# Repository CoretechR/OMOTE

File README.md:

# OMOTE - Open Universal Remote - Firmware

[][link1]

## Overview

This it the ESP32 arduino based firmware for the OMOTE - Open Universal Remote.

To run this firmware, you have two options
*  run it on the [OMOTE ESP32 Hardware](https://github.com/OMOTE-Community/OMOTE-Hardware/)
*  run it in the simulator on Linux, macOs or Windows

### The state of this project

#### Software
The software can be adjusted to your needs. You can add your own amplifier, TV and media player. Smart home devices can be controlled with MQTT. The software is an example made up of:
* a TV and an amplifier controlled with infrared
* a Fire TV media player controlled with BLE (bluetooth keyboard)
* some smart home devices controlled with MQTT
* an IR receiver for decoding the IR codes from your remote

Please see the [wiki on how to understand and modify the firmware.](https://github.com/OMOTE-Community/OMOTE-Firmware/wiki/How-to-understand-and-modify-the-firmware)

You need to have PlatformIO running, and you need to know how to compile and flash your own firmware with PlatformIO. There is no prebuild firmware.

The remote can be charged and programmed via its USB-C port. Open the PlatformIO project to compile and upload the code to the ESP32.

As a long term goal, maybe a prebuild firmware will be published, where you can configure your OMOTE via a web interface.

### LVGL GUI simulator for Windows, Linux, and macOS

A simulator for running the LVGL UI on your local Windows, Linux, or macOS machine is available.

You can run the simulator in Visual Studio Code with PlatformIO. No need for any other compiler or development environment (no Visual Studio needed as often done in other LVGL simulators).
<div align="center">
  
</div>

For details, please see the [wiki for the software simulator for fast creating and testing of LVGL GUIs.](https://github.com/OMOTE-Community/OMOTE-Firmware/wiki/Software-simulator-for-fast-creating-and-testing-of-LVGL-GUIs)

### To Dos for software

Long term goals (not yet scheduled)
- [ ] Add an interface for graphically editing the configuration
- [ ] Store the configuration in Flash (e.g. as a editable json file)

See the [open issues](https://github.com/OMOTE-Community/OMOTE-Firmware/issues) and [discussions](https://github.com/OMOTE-Community/OMOTE-Firmware/discussions) for a full list of proposed features (and known issues).

## Contributing

If you have a suggestion for an improvement, please fork the repo and create a pull request. You can also simply open an issue or for more general feature requests, head over to the [discussions](https://github.com/OMOTE-Community/OMOTE-Firmware/discussions).

## License

Distributed under the GPL v3 License. See [LICENSE](https://github.com/OMOTE-Community/OMOTE-Firmware/blob/main/LICENSE) for more information.

## Contact

[][link1]

Join the OMOTE Discord: [https://discord.gg/5PnYFAsKsG](https://discord.gg/5PnYFAsKsG)

[link1]: https://discord.gg/5PnYFAsKsG

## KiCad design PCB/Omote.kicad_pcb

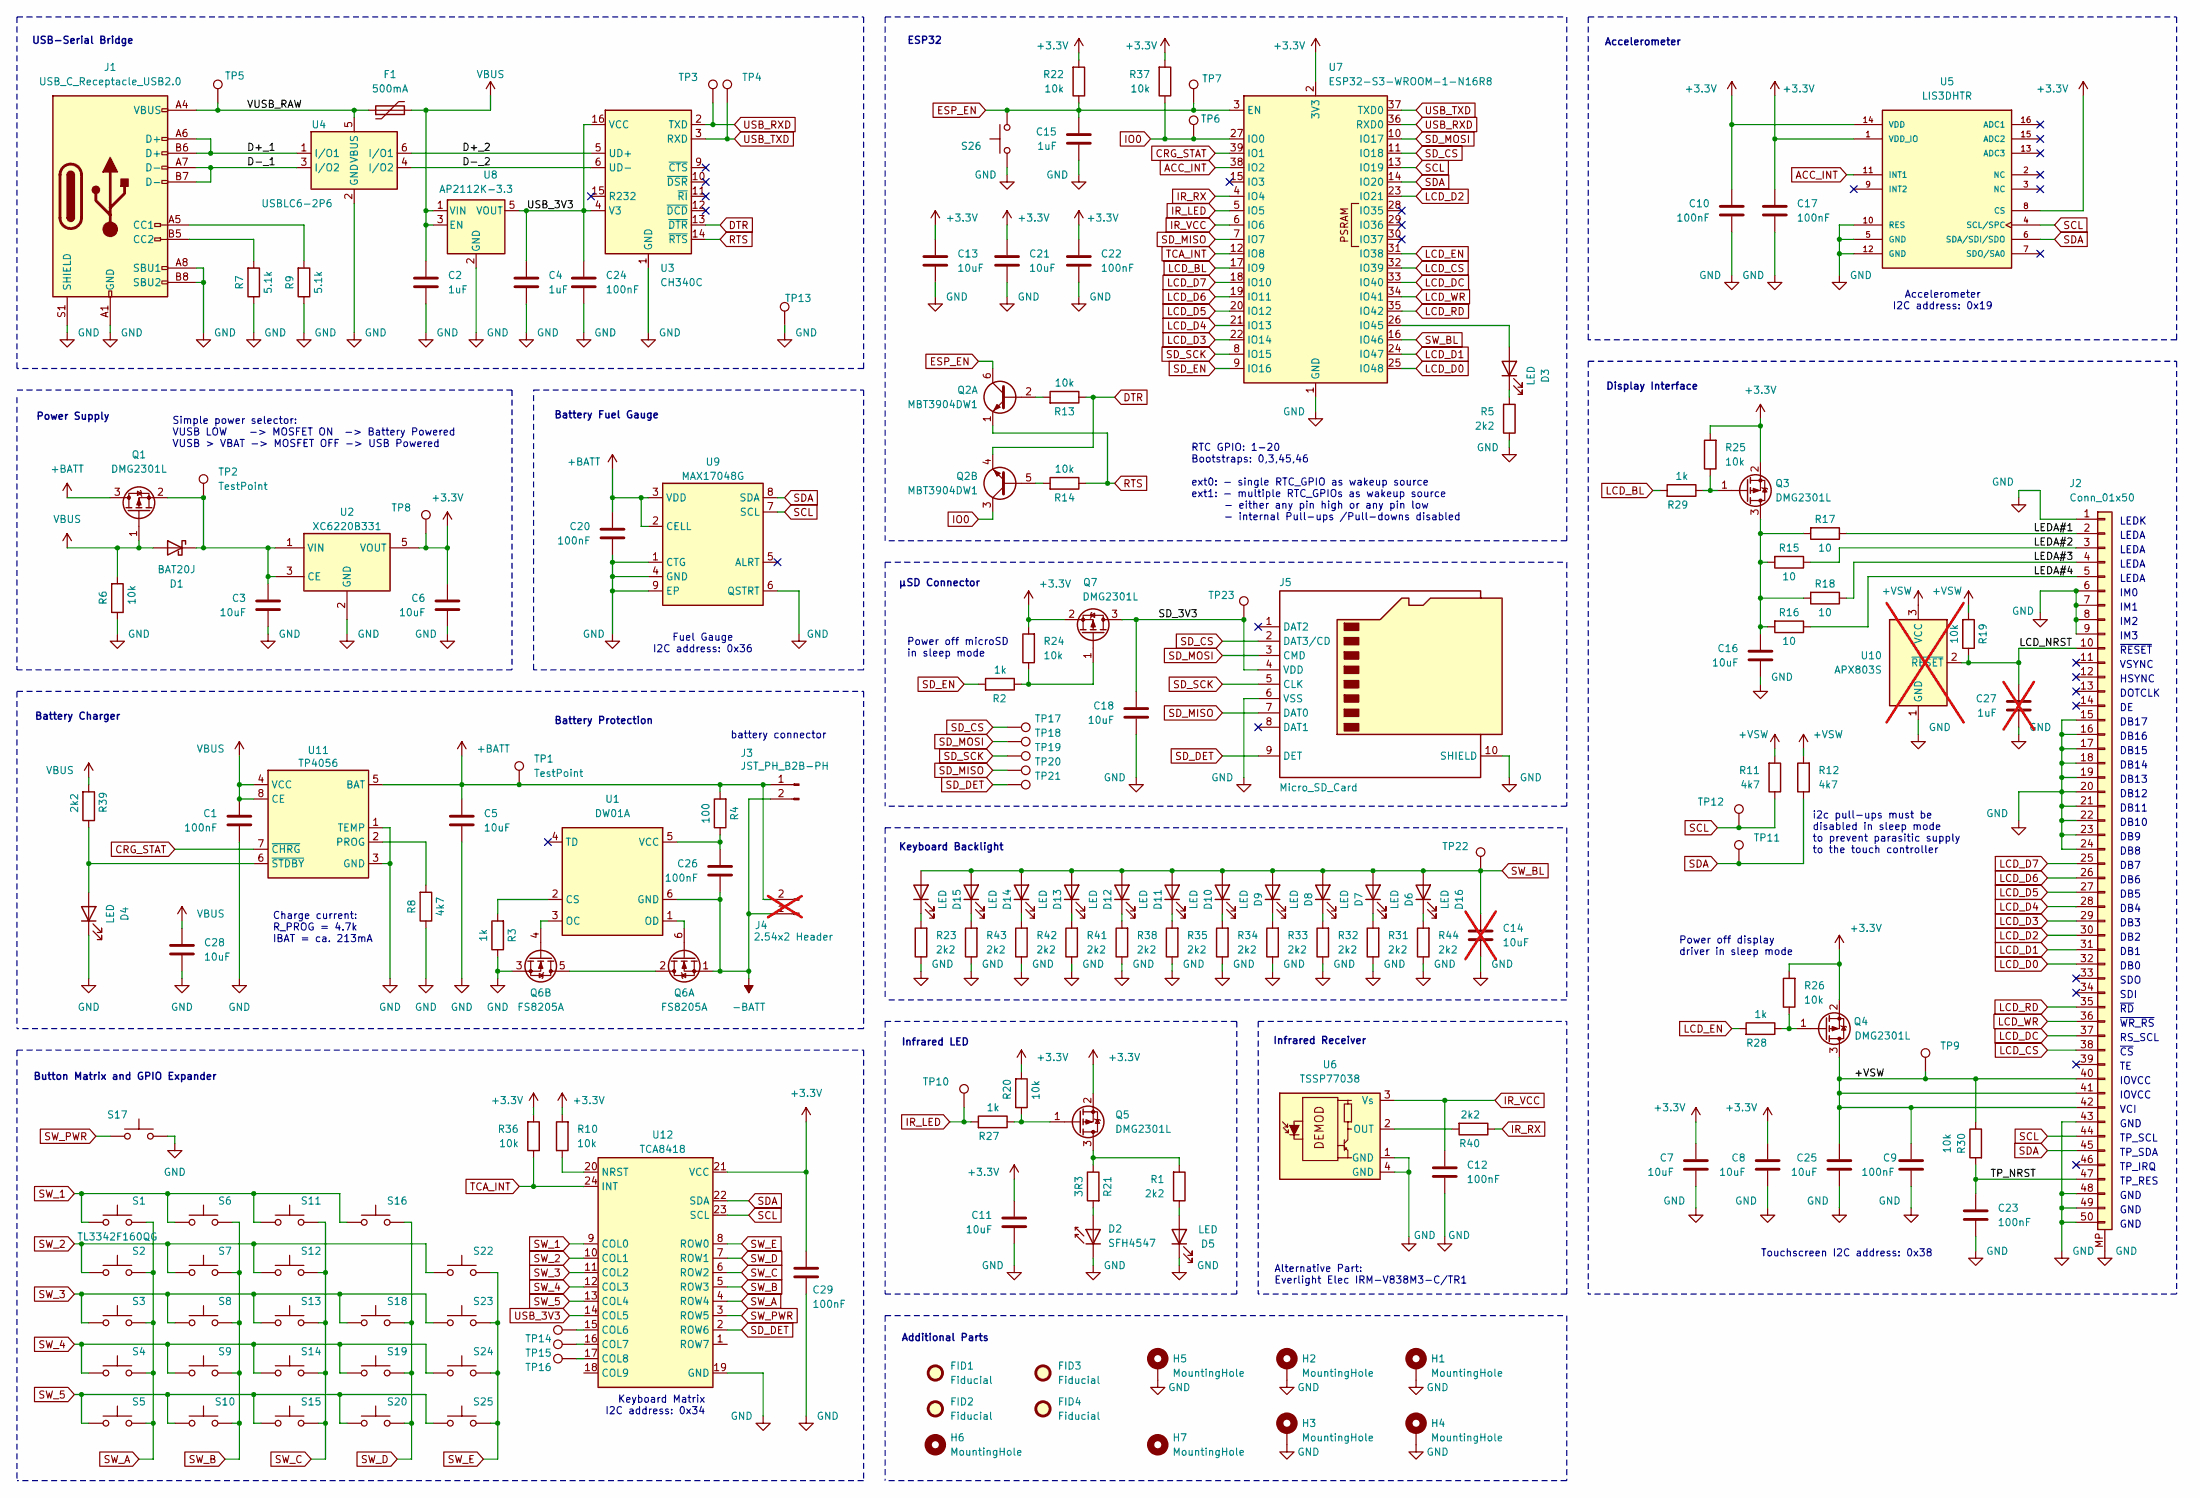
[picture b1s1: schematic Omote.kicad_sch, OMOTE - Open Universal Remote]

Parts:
C1, C9, C10, C12, C17, C20, C22, C23, C24, C26, C29: 100nF; C_0603_1608Metric; LCSC C1591
C2, C4, C15: 1uF; C_0603_1608Metric; LCSC C15849
C3, C5, C6, C7, C8, C11, C13, C16, C18, C21, C25, C28: 10uF; C_0805_2012Metric; LCSC C15850
C14: 10uF; C_0805_2012Metric; LCSC C15850; not fitted
C27: 1uF; C_0603_1608Metric; not fitted
D1: BAT20J; D_SOD-323; LCSC C155590
D2: SFH4547; LED_5mm_Side_Mount; LCSC C405273
D3, D4, D5: LED; LED_0603_1608Metric; LCSC C965807
D6, D7, D8, D9, D10, D11, D12, D13, D14, D15, D16: LED; LED_0603_1608Metric; LCSC C84265
F1: 500mA; Fuse_1206_3216Metric_Pad1.42x1.75mm_HandSolder; LCSC C220146
FID1, FID2, FID3, FID4: Fiducial; Fiducial_1mm_Mask2mm
H1, H2, H3, H5: MountingHole; MountingHole_3.2mm_M3_Pad_Via
H4: MountingHole; MountingHole_3.2mm_M3
H6, H7: MountingHole; MountingHole_2.5mm
J1: USB_C_Receptacle_USB2.0; USB_C_Receptacle_HRO_TYPE-C-31-M-12; LCSC C2982555
J2: Conn_01x50; TFT_2.83IN_240X320_50PIN; LCSC C11098
J3: JST_PH_B2B-PH; JST_PH_B2B-PH-SM4-TB_1x02-1MP_P2.00mm_Vertical; LCSC C160352
J4: 2.54x2 Header; PinHeader_1x02_P2.54mm_Vertical; not fitted
J5: Micro_SD_Card; MicroSD Slot TF-01A; LCSC C20613191
Q1, Q3, Q4, Q5, Q7: DMG2301L; SOT-23; LCSC C102619
Q2: MBT3904DW1; SOT-363_SC-70-6; LCSC C110150
Q6: FS8205A; SOT-23-6; LCSC C908265
R1, R5, R23, R31, R32, R33, R34, R35, R38, R39, R40, R41, R42, R43, R44: 2k2; R_0603_1608Metric; LCSC C114662
R2, R3, R27, R28, R29: 1k; R_0603_1608Metric; LCSC C22548
R4: 100; R_0603_1608Metric; LCSC C125923
R6, R10, R13, R14, R19, R20, R22, R24, R25, R26, R30, R36, R37: 10k; R_0603_1608Metric; LCSC C98220
R7, R9: 5.1k; R_0603_1608Metric; LCSC C105580
R8, R11, R12: 4k7; R_0603_1608Metric; LCSC C99782
R15, R16, R17, R18: 10; R_0603_1608Metric; LCSC C109318
R21: 3R3; R_0805_2012Metric; LCSC C2849062
S1, S2, S3, S4, S5, S6, S7, S8, S9, S10, S11, S12, S13, S14, S15, S16, S17, S18, S19, S20, S22, S23, S24, S25, S26: TL3342F160QG; SW_SPST_TL3342; LCSC C778172
TP1, TP2, TP3, TP4, TP5, TP6, TP7, TP8, TP9, TP10, TP11, TP12, TP13, TP14, TP15, TP16, TP17, TP18, TP19, TP20, TP21, TP22, TP23: TestPoint; TestPoint_Pad_D1.5mm
U1: DW01A; SOT-23-6; LCSC C18164398
U2: XC6220B331; SOT-23-5; LCSC C86534
U3: CH340C; SOIC-16_3.9x9.9mm_P1.27mm; LCSC C84681
U4: USBLC6-2P6; SOT-666; LCSC C2827693
U5: LIS3DHTR; XDCR_LIS3DHTR; PARTREV 2; LCSC C15134
U6: TSSP77038; Heimdall vertical; LCSC C3291489
U7: ESP32-S3-WROOM-1-N16R8; ESP32-S3-WROOM-1; LCSC C2913202
U8: AP2112K-3.3; SOT-23-5; LCSC C51118
U9: MAX17048G; TDFN-8-1EP_2x2mm_P0.5mm_EP0.8x1.2mm; LCSC C2682616
U10: APX803S; SOT-23; not fitted
U11: TP4056; Infineon_PG-DSO-8-27_3.9x4.9mm_EP2.65x3mm; LCSC C725790
U12: TCA8418; HVQFN-24-1EP_4x4mm_P0.5mm_EP2.5x2.5mm; LCSC C138713

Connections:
+3.3V: C6.1, C7.2, C8.2, C10.1, C11.2, C13.2, C17.1, C21.2, C22.1, C29.1, Q3.2 (S), Q4.2 (S), Q5.2 (S), Q7.2 (S), R10.2, R20.2, R22.2, R24.2, R25.2, R26.2, R36.2, R37.2, TP8.1, U2.5 (VOUT), U5.1 (VDD_IO), U5.8 (CS), U5.14 (VDD), U7.2 (3V3), U12.21 (VCC)
+BATT: C5.2, C20.1, J3.1, J4.2, Q1.3 (D), R4.2, TP1.1, U9.2 (CELL), U9.3 (VDD), U11.5 (BAT)
+VSW: C9.1, C25.2, J2.40, J2.41, J2.42 (Pin_41), Q4.3 (D), R11.2, R12.2, R19.2, R30.1, TP9.1, U10.3 (VCC)
-BATT: C26.2, J3.2, J4.1, Q6.1 (S), U1.6 (GND)
/D+_1: J1.A6 (D+), J1.B6 (D+), U4.1 (I/O1)
/D+_2: U3.5 (UD+), U4.6 (I/O1)
/D-_1: J1.A7 (D-), J1.B7 (D-), U4.3 (I/O2)
/D-_2: U3.6 (UD-), U4.4 (I/O2)
/LCD_NRST: C27.2, J2.10, R19.1, U10.2 (~RESET)
/LEDA#1: J2.2, R17.1
/LEDA#2: J2.3, R15.1
/LEDA#3: J2.4, R18.1
/LEDA#4: J2.5, R16.1
/SD_3V3: C18.2, J5.4 (VDD), Q7.3 (D), TP23.1
/TP_NRST: C23.2, J2.47, R30.2
/VUSB_RAW: F1.1, J1.A4 (VBUS), J1.A9 (VBUS), J1.B4 (VBUS), J1.B9 (VBUS), TP5.1, U4.5 (VBUS)
ACC_INT: U5.11 (INT1), U7.38 (IO2)
CRG_STAT: U7.39 (IO1), U11.7 (~CHRG)
DTR: Q2.4 (E2), R13.1, U3.13 (~DTR)
ESP_EN: C15.2, Q2.6 (C1), R22.1, S26.2, TP7.1, U7.3 (EN)
GND: C1.2, C2.2, C3.1, C4.2, C5.1, C6.2, C7.1, C8.1, C9.2, C10.2, C11.1, C12.2, C13.1, C14.1, C15.1, C16.1, C17.2, C18.1, C20.2, C21.1, C22.2, C23.1, C24.2, C25.1, C27.1, C28.1, C29.2, D2.1 (K), D4.1 (K), D5.1 (K), H1.1, H2.1, H3.1, H4.1, H5.1, J1.A1 (GND), J1.A8 (SBU1), J1.A12 (GND), J1.B1 (GND), J1.B8 (SBU2), J1.B12 (GND), J1.S1 (SHIELD), J2.1, J2.6, J2.7, J2.8, J2.9, J2.15, J2.16, J2.17, J2.18, J2.19, J2.20, J2.21, J2.22, J2.23, J2.24, J2.43, J2.48, J2.49, J2.50, J2.MP, J5.6 (VSS), J5.10 (SHIELD), Q6.3 (S), R3.1, R5.1, R6.1, R7.1, R8.1, R9.1, R23.1, R31.1, R32.1, R33.1, R34.1, R35.1, R38.1, R41.1, R42.1, R43.1, R44.1, S17.1, S26.1, TP13.1, U2.2 (GND), U3.1 (GND), U4.2 (GND), U5.5 (GND), U5.10 (RES), U5.12 (GND), U6.1 (GND), U6.4 (GND), U7.1 (GND), U7.40 (GND), U7.41 (GND), U8.2 (GND), U9.1 (CTG), U9.4 (GND), U9.6 (QSTRT), U9.9 (EP), U10.1 (GND), U11.1 (TEMP), U11.3 (GND), U11.9 (GND), U12.19 (GND)
IO0: Q2.3 (C2), R37.1, TP6.1, U7.27 (IO0)
IR_LED: R27.2, TP10.1, U7.5 (IO5)
IR_RX: R40.1, U7.4 (IO4)
IR_VCC: C12.1, U6.3 (Vs), U7.6 (IO6)
LCD_BL: R29.2, U7.17 (IO9)
LCD_CS: J2.38, U7.32 (IO39)
LCD_D0: J2.32, U7.25 (IO48)
LCD_D1: J2.31, U7.24 (IO47)
LCD_D2: J2.30, U7.23 (IO21)
LCD_D3: J2.29, U7.22 (IO14)
LCD_D4: J2.28, U7.21 (IO13)
LCD_D5: J2.27, U7.20 (IO12)
LCD_D6: J2.26, U7.19 (IO11)
LCD_D7: J2.25, U7.18 (IO10)
LCD_DC: J2.37, U7.33 (IO40)
LCD_EN: R28.2, U7.31 (IO38)
LCD_RD: J2.35, U7.35 (IO42)
LCD_WR: J2.36, U7.34 (IO41)
unnamed: C3.2, D1.1 (K), Q1.2 (S), TP2.1, U2.1 (VIN), U2.3 (CE)
unnamed: D2.2 (A), R21.2
unnamed: D3.2 (A), U7.26 (IO45)
unnamed: D3.1 (K), R5.2
unnamed: D4.2 (A), R39.1, U11.6 (~STDBY)
unnamed: D5.2 (A), R1.1
unnamed: D6.1 (K), R31.2
unnamed: D7.1 (K), R32.2
unnamed: D8.1 (K), R33.2
unnamed: D9.1 (K), R34.2
unnamed: D10.1 (K), R35.2
unnamed: D11.1 (K), R38.2
unnamed: D12.1 (K), R41.2
unnamed: D13.1 (K), R42.2
unnamed: D14.1 (K), R43.2
unnamed: D15.1 (K), R23.2
unnamed: D16.1 (K), R44.2
unnamed: J1.A5 (CC1), R9.2
unnamed: J1.B5 (CC2), R7.2
unnamed: Q2.2 (B1), R13.2
unnamed: Q2.5 (B2), R14.2
unnamed: C16.2, Q3.3 (D), R15.2, R16.2, R17.2, R18.2
unnamed: Q3.1 (G), R25.1, R29.1
unnamed: Q4.1 (G), R26.1, R28.1
unnamed: Q5.3 (D), R1.2, R21.1
unnamed: Q5.1 (G), R20.1, R27.1
unnamed: Q6.2 (D), Q6.5 (D)
unnamed: Q6.6 (G), U1.1 (OD)
unnamed: Q6.4 (G), U1.3 (OC)
unnamed: Q7.1 (G), R2.1, R24.1
unnamed: R3.2, U1.2 (CS)
unnamed: C26.1, R4.1, U1.5 (VCC)
unnamed: R40.2, U6.2 (OUT)
unnamed: R8.2, U11.2 (PROG)
unnamed: TP14.1, U12.15 (COL6)
unnamed: TP15.1, U12.16 (COL7)
unnamed: TP16.1, U12.17 (COL8)
unnamed: R10.1, U12.20 (NRST)
RTS: Q2.1 (E1), R14.1, U3.14 (~RTS)
SCL: J2.44, R11.1, TP12.1, U5.4 (SCL/SPC), U7.13 (IO19), U9.7 (SCL), U12.23 (SCL)
SDA: J2.45, R12.1, TP11.1, U5.6 (SDA/SDI/SDO), U7.14 (IO20), U9.8 (SDA), U12.22 (SDA)
SD_CS: J5.2 (DAT3/CD), TP17.1, U7.11 (IO18)
SD_DET: J5.9 (DET), TP21.1, U12.2 (ROW6)
SD_EN: R2.2, U7.9 (IO16)
SD_MISO: J5.7 (DAT0), TP20.1, U7.7 (IO7)
SD_MOSI: J5.3 (CMD), TP18.1, U7.10 (IO17)
SD_SCK: J5.5 (CLK), TP19.1, U7.8 (IO15)
SW_1: S1.1, S6.1, S11.1, S16.1, U12.9 (COL0)
SW_2: S2.1, S7.1, S12.1, S22.1, U12.10 (COL1)
SW_3: S3.1, S8.1, S13.1, S18.1, S23.1, U12.11 (COL2)
SW_4: S4.1, S9.1, S14.1, S19.1, S24.1, U12.12 (COL3)
SW_5: S5.1, S10.1, S15.1, S20.1, S25.1, U12.13 (COL4)
SW_A: S1.2, S2.2, S3.2, S4.2, S5.2, U12.4 (ROW4)
SW_B: S6.2, S7.2, S8.2, S9.2, S10.2, U12.5 (ROW3)
SW_BL: C14.2, D6.2 (A), D7.2 (A), D8.2 (A), D9.2 (A), D10.2 (A), D11.2 (A), D12.2 (A), D13.2 (A), D14.2 (A), D15.2 (A), D16.2 (A), TP22.1, U7.16 (IO46)
SW_C: S11.2, S12.2, S13.2, S14.2, S15.2, U12.6 (ROW2)
SW_D: S16.2, S18.2, S19.2, S20.2, U12.7 (ROW1)
SW_E: S22.2, S23.2, S24.2, S25.2, U12.8 (ROW0)
SW_PWR: S17.2, U12.3 (ROW5)
TCA_INT: R36.1, U7.12 (IO8), U12.24 (INT)
USB_3V3: C4.1, C24.1, U3.4 (V3), U3.16 (VCC), U8.5 (VOUT), U12.14 (COL5)
USB_RXD: TP3.1, U3.2 (TXD), U7.36 (RXD0)
USB_TXD: TP4.1, U3.3 (RXD), U7.37 (TXD0)
VBUS: C1.1, C2.1, C28.2, D1.2 (A), F1.2, Q1.1 (G), R6.2, R39.2, U8.1 (VIN), U8.3 (EN), U11.4 (VCC), U11.8 (CE)

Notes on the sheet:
DB6
Accelerometer I2C address: 0x19
DB11
DB14
IM2
DB10
Infrared Receiver
Display Interface
LEDA
DB0
GND
DB16
Alternative Part: Everlight Elec IRM-V838M3-C/TR1
TP_RES
TP_IRQ
LEDK
IM1
IOVCC
Battery Fuel Gauge
~{RESET}
ESP32
RTC GPIO: 1-20 Bootstraps: 0,3,45,46 ext0: - single RTC_GPIO as wakeup source ext1: - multiple RTC_GPIOs as wakeup source - either any pin high or any pin low - internal Pull-ups /Pull-downs disabled
Battery Protection
IM3
DB5
Additional Parts
USB-Serial Bridge
Charge current: R_PROG = 4.7k IBAT = ca. 213mA
DB17
TP_SDA
DB7
DB12
DB1
DOTCLK
~{WR_RS}
Infrared LED
µSD Connector
SDI
DB13
DB4

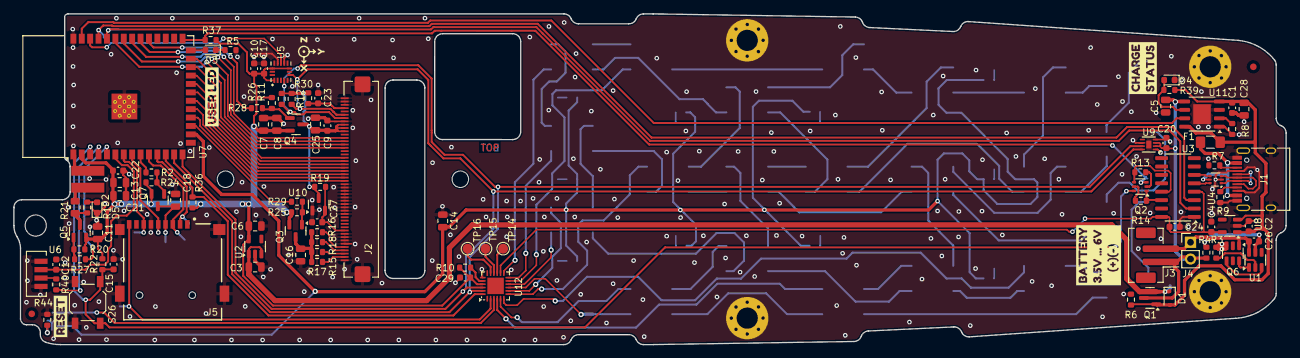
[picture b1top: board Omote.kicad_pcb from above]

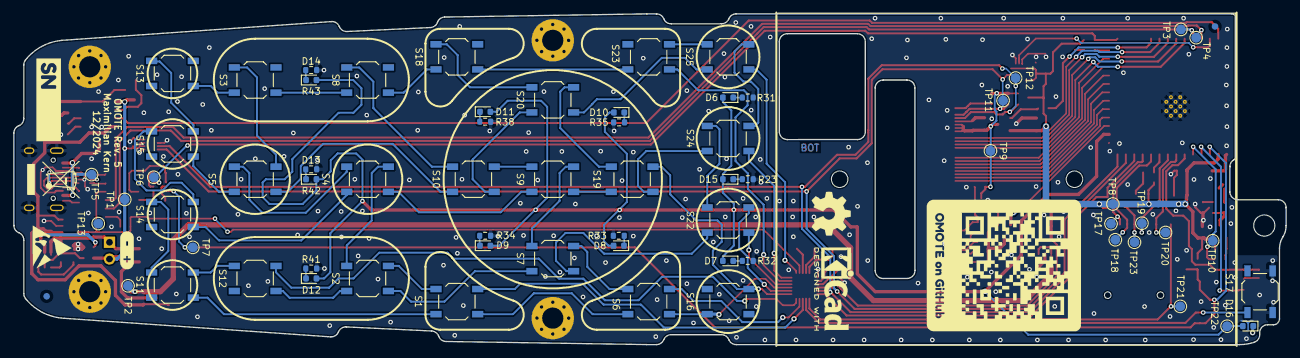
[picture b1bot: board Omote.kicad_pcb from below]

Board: 2 copper layers, 192.4 x 50.0 mm, 181 parts (69 on the bottom side), 103 nets.

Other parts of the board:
kibuzzard-63D97EAF: G***; kibuzzard-63D97EAF
kibuzzard-64A91BF0: G***; kibuzzard-64A91BF0
kibuzzard-64A91C1C: G***; kibuzzard-64A91C1C
kibuzzard-64A91C24: G***; kibuzzard-64A91C24
kibuzzard-643EE5B9: G***; kibuzzard-643EE5B9
kibuzzard-643EE8B3: G***; kibuzzard-643EE8B3
kibuzzard-643EE46C: G***; kibuzzard-643EE46C
kibuzzard-643EE600: G***; kibuzzard-643EE600
kibuzzard-644014FA: G***; kibuzzard-644014FA

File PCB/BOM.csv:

Item,Quantity,Designator,Value,Footprint,LCSC Part #,Comment
1,11,C1; C10; C12; C17; C20; C22; C23; C24; C26; C29; C9,100nF,0603,C1591,
2,12,C11; C13; C16; C18; C21; C25; C28; C3; C5; C6; C7; C8,10uF,805,C15850,
3,3,C15; C2; C4,1uF,0603,C15849,
4,1,D1,BAT20J,D_SOD-323,C155590,
5,14,D10; D11; D12; D13; D14; D15; D16; D3; D4; D5; D6; D7; D8; D9,LED,0603,C965807,
6,1,D2,SFH4547,LED_5mm_Side_Mount,C405273,
7,1,F1,500mA,1206,C220146,
8,1,J1,USB_C_Receptacle_USB2.0,USB_C_Receptacle_HRO_TYPE-C-31-M-12,C2982555,
9,1,J2,Conn_01x50,TFT_2.83IN_240X320_50PIN,C11098,
10,1,J3,JST_PH_B2B-PH,JST_PH_B2B-PH-SM4-TB_1x02-1MP_P2.00mm_Vertical,C160352,
11,1,J5,Micro_SD_Card,MicroSD Slot TF-01A,C20613191,
12,5,Q1; Q3; Q4; Q5; Q7,DMG2301L,SOT-23,C102619,
13,1,Q2,MBT3904DW1,SOT-363_SC-70-6,C110150,
14,1,Q6,FS8205A,SOT-23-6,C908265,
15,15,R1; R23; R31; R32; R33; R34; R35; R38; R39; R40; R41; R42; R43; R44; R5,2k2,0603,C114662,
16,13,R10; R13; R14; R19; R20; R22; R24; R25; R26; R30; R36; R37; R6,10k,0603,C98220,
17,3,R11; R12; R8,4k7,0603,C99782,
18,4,R15; R16; R17; R18,10,0603,C109318,
19,1,R21,3R3,805,C2849062,
20,5,R2; R3; R27; R28; R29,1k,0603,C22548,
21,1,R4,100,0603,C125923,
22,2,R7; R9,5.1k,0603,C105580,
23,25,S1; S10; S11; S12; S13; S14; S15; S16; S17; S18; S19; S2; S20; S22; S23; S24; S25; S26; S3; S4; S5; S6; S7; S8; S9,TL3342F160QG,SW_SPST_TL3342,C778172 ,
24,1,U1,DW01A,SOT-23-6,C18164398,
25,1,U11,TP4056,Infineon_PG-DSO-8-27_3.9x4.9mm_EP2.65x3mm,C725790,
26,1,U12,TCA8418,HVQFN-24-1EP_4x4mm_P0.5mm_EP2.5x2.5mm,C138713,
27,1,U2,XC6220B331,SOT-23-5,C86534,
28,1,U3,CH340C,SOIC-16_3.9x9.9mm_P1.27mm,C84681,
29,1,U4,USBLC6-2P6,SOT-666,C2827693,
30,1,U5,LIS3DHTR,XDCR_LIS3DHTR,C15134,
31,1,U6,TSSP77038,Heimdall vertical,C3291489,
32,1,U7,ESP32-S3-WROOM-1-N16R8,ESP32-S3-WROOM-1,C2913202,
33,1,U8,AP2112K-3.3,SOT-23-5,C51118,
34,1,U9,MAX17048G,TDFN-8-1EP_2x2mm_P0.5mm_EP0.8x1.2mm,C2682616,
,,,,,,
36,1,,2.8 TFT Display - 240x320 with Capacitive Touchscreen,,,https://www.adafruit.com/product/2770
37,1,,3.7V 2000mAh LiPo,,,https://eckstein-shop.de/LiPo-Akku-Lithium-Ion-Polymer-Batte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

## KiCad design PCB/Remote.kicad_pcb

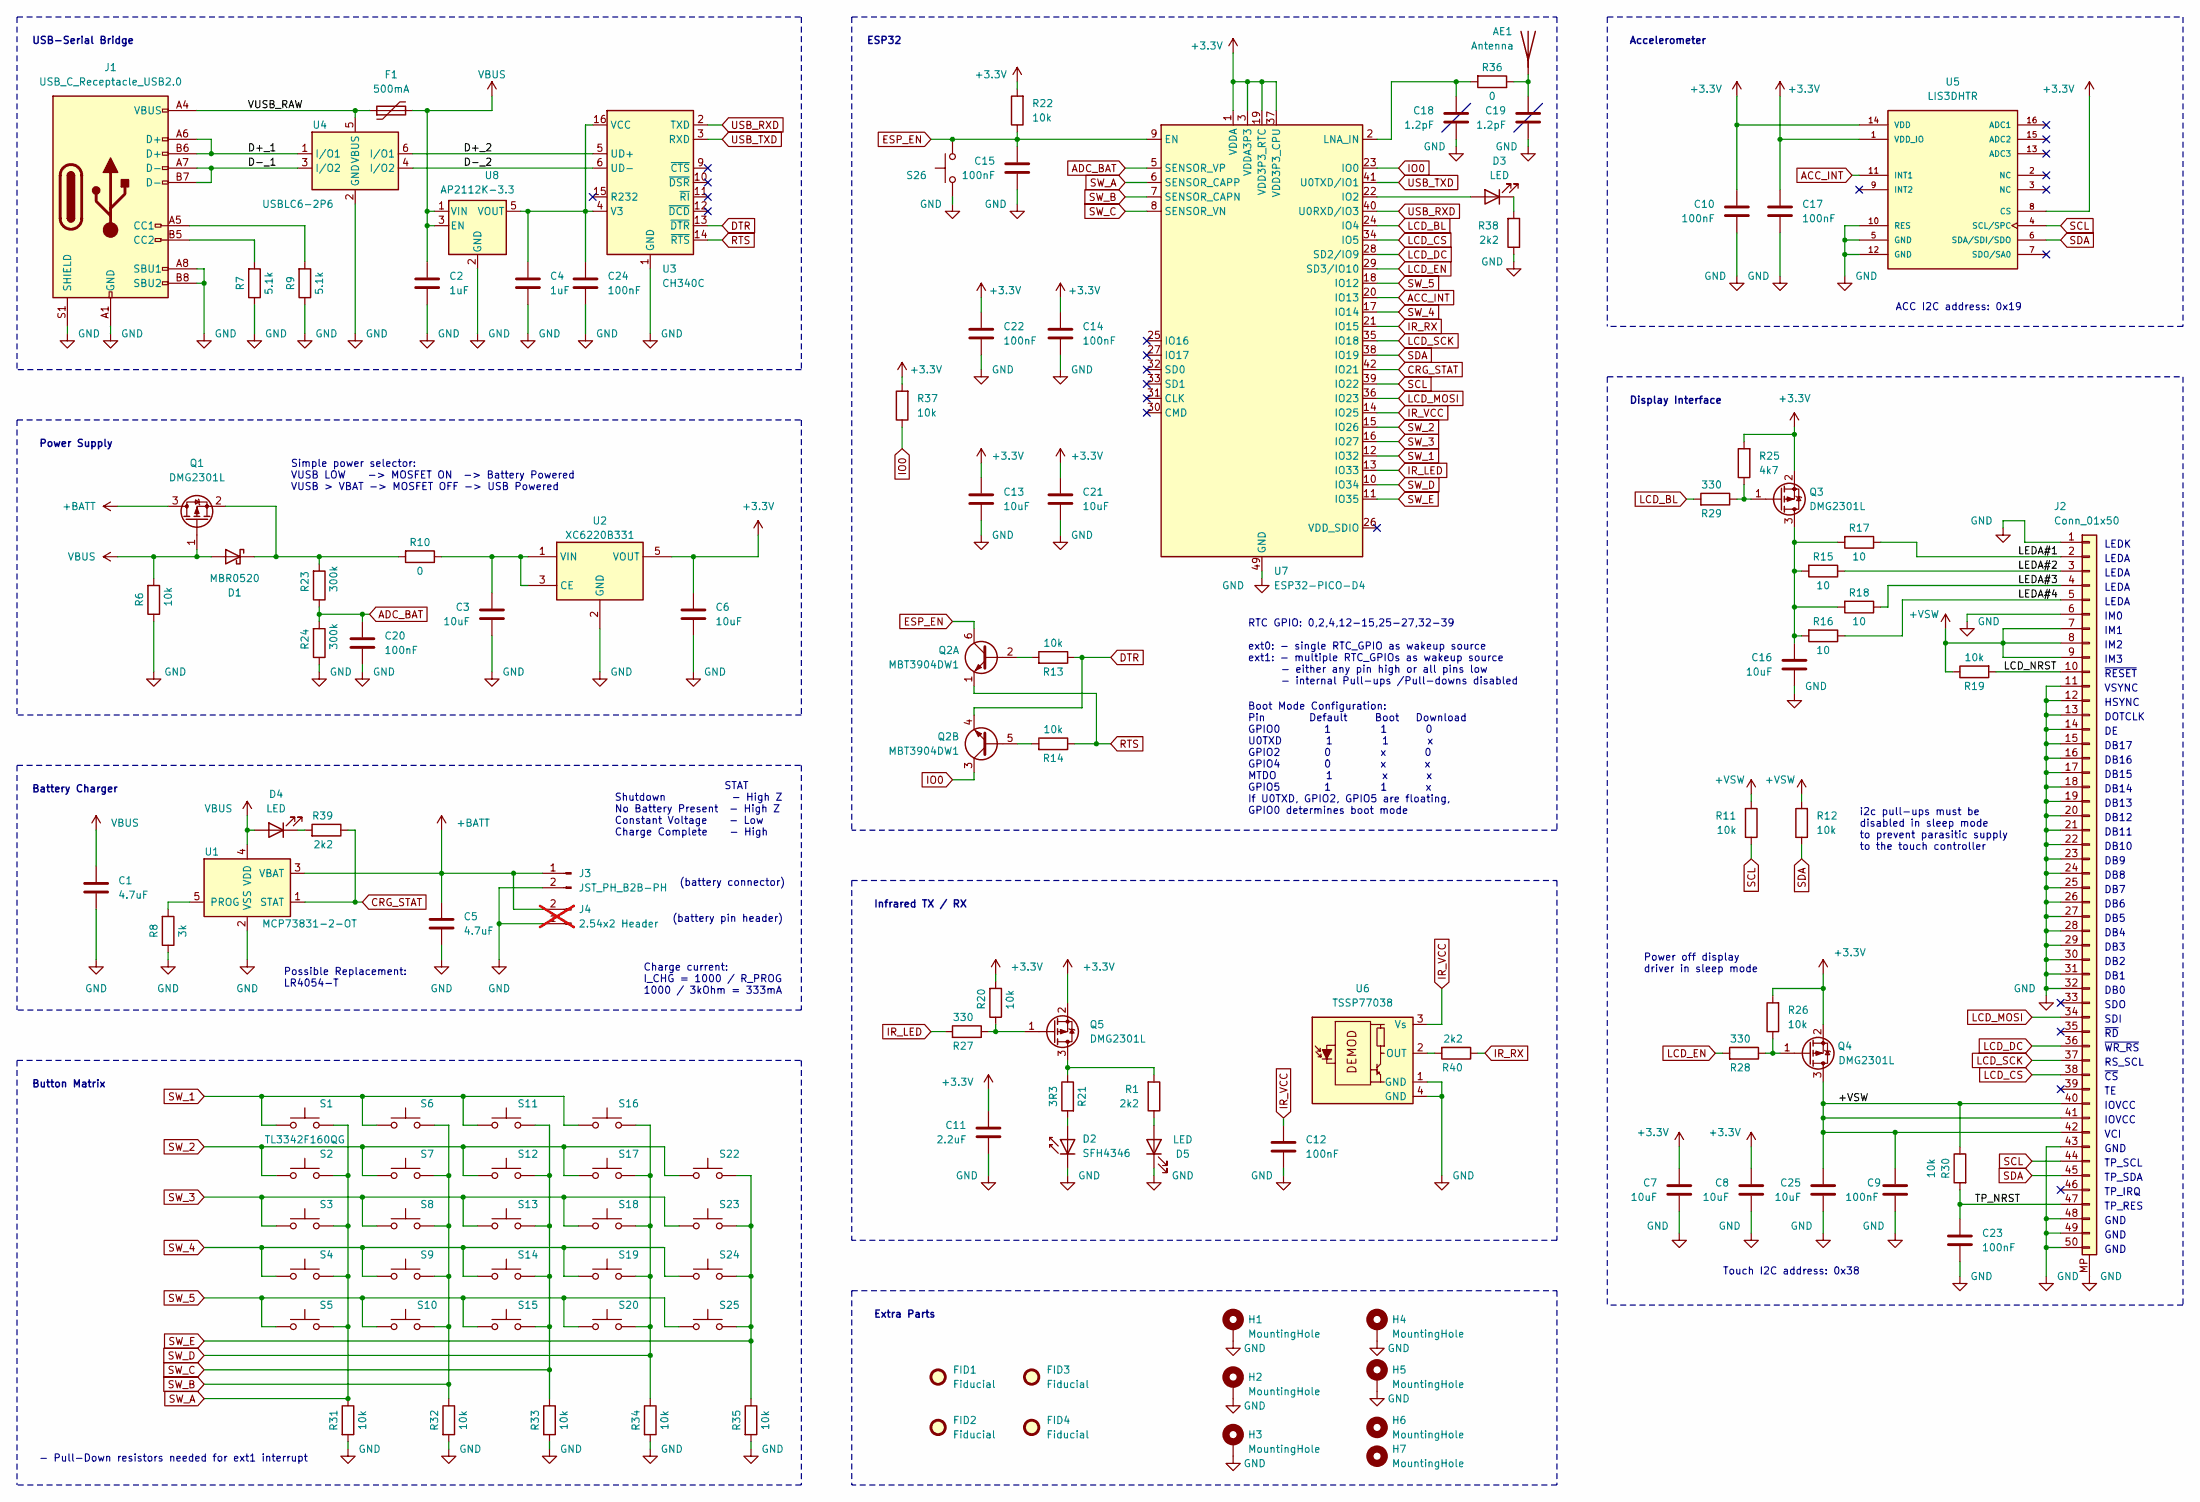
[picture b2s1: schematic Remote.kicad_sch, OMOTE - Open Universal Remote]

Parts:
AE1: Antenna; RFANT5220110A2T
C1, C5: 4.7uF; C_0603_1608Metric
C2, C4: 1uF; C_0603_1608Metric
C3, C6, C7, C8, C13, C16, C21, C25: 10uF; C_0805_2012Metric
C9, C10, C12, C14, C15, C17, C20, C22, C23, C24: 100nF; C_0603_1608Metric
C11: 2.2uF; C_0603_1608Metric
C18, C19: 1.2pF; C_0603_1608Metric
D1: MBR0520; D_SOD-123
D2: SFH4346; LED_5mm_Side_Mount
D3, D4, D5: LED; LED_0603_1608Metric
F1: 500mA; Fuse_1206_3216Metric_Pad1.42x1.75mm_HandSolder
FID1, FID2, FID3, FID4: Fiducial; Fiducial_1mm_Mask2mm
H1, H2, H3, H4, H5: MountingHole; MountingHole_3.2mm_M3_Pad_Via
H6, H7: MountingHole; MountingHole_2.5mm
J1: USB_C_Receptacle_USB2.0; USB_C_Receptacle_HRO_TYPE-C-31-M-12
J2: Conn_01x50; TFT_2.83IN_240X320_50PIN
J3: JST_PH_B2B-PH; JST_PH_B2B-PH-SM4-TB_1x02-1MP_P2.00mm_Vertical
J4: 2.54x2 Header; PinHeader_1x02_P2.54mm_Vertical; not fitted
Q1, Q3, Q4, Q5: DMG2301L; SOT-23
Q2: MBT3904DW1; SOT-363_SC-70-6
R1, R38, R39, R40: 2k2; R_0603_1608Metric
R6, R11, R12, R13, R14, R19, R20, R22, R26, R30, R31, R32, R33, R34, R35, R37: 10k; R_0603_1608Metric
R7, R9: 5.1k; R_0603_1608Metric
R8: 3k; R_0603_1608Metric
R10, R36: 0; R_0603_1608Metric
R15, R16, R17, R18: 10; R_0603_1608Metric
R21: 3R3; R_0805_2012Metric
R23, R24: 300k; R_0603_1608Metric
R25: 4k7; R_0603_1608Metric
R27, R28, R29: 330; R_0603_1608Metric
S1, S2, S3, S4, S5, S6, S7, S8, S9, S10, S11, S12, S13, S14, S15, S16, S17, S18, S19, S20, S22, S23, S24, S25, S26: TL3342F160QG; SW_SPST_TL3342
U1: MCP73831-2-OT; SOT-23-5
U2: XC6220B331; SOT-23-5
U3: CH340C; SOIC-16_3.9x9.9mm_P1.27mm
U4: USBLC6-2P6; SOT-666
U5: LIS3DHTR; XDCR_LIS3DHTR; PARTREV 2
U6: TSSP77038; Heimdall vertical
U7: ESP32-PICO-D4; QFN-48-1EP_7x7mm_P0.5mm_EP5.3x5.3mm_ThermalVias_MR
U8: AP2112K-3.3; SOT-23-5

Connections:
+3.3V: C6.1, C7.2, C8.2, C10.1, C11.1, C13.2, C14.1, C17.1, C21.2, C22.1, Q3.2 (S), Q4.2 (S), Q5.2 (S), R20.2, R22.2, R25.2, R26.2, R37.2, U2.5 (VOUT), U5.1 (VDD_IO), U5.8 (CS), U5.14 (VDD), U7.1 (VDDA), U7.3 (VDDA3P3), U7.4 (VDDA3P3), U7.19 (VDD3P3_RTC), U7.37 (VDD3P3_CPU), U7.43 (VDDA), U7.46 (VDDA)
+BATT: C5.2, J3.1, J4.2, Q1.3 (D), U1.3 (VBAT)
+VSW: C9.1, C25.2, J2.7, J2.8, J2.9, J2.40, J2.41, J2.42 (Pin_41), Q4.3 (D), R11.2, R12.2, R19.1, R30.1
/D+_1: J1.A6 (D+), J1.B6 (D+), U4.1 (I/O1)
/D+_2: U3.5 (UD+), U4.6 (I/O1)
/D-_1: J1.A7 (D-), J1.B7 (D-), U4.3 (I/O2)
/D-_2: U3.6 (UD-), U4.4 (I/O2)
/LCD_NRST: J2.10, R19.2
/LEDA#1: J2.2, R17.1
/LEDA#2: J2.3, R15.1
/LEDA#3: J2.4, R18.1
/LEDA#4: J2.5, R16.1
/TP_NRST: C23.2, J2.47, R30.2
/VUSB_RAW: F1.1, J1.A4 (VBUS), J1.A9 (VBUS), J1.B4 (VBUS), J1.B9 (VBUS), U4.5 (VBUS)
ACC_INT: U5.11 (INT1), U7.20 (IO13)
ADC_BAT: C20.1, R23.1, R24.2, U7.5 (SENSOR_VP)
CRG_STAT: R39.1, U1.1 (STAT), U7.42 (IO21)
DTR: Q2.4 (E2), R13.1, U3.13 (~DTR)
ESP_EN: C15.2, Q2.6 (C1), R22.1, S26.2, U7.9 (EN)
GND: C1.1, C2.2, C3.1, C4.2, C5.1, C6.2, C7.1, C8.1, C9.2, C10.2, C11.2, C12.2, C13.1, C14.2, C15.1, C16.1, C17.2, C18.1, C19.1, C20.2, C21.1, C22.2, C23.1, C24.2, C25.1, D2.1 (K), D5.1 (K), H1.1, H2.1, H3.1, H4.1, H5.1, J1.A1 (GND), J1.A8 (SBU1), J1.A12 (GND), J1.B1 (GND), J1.B8 (SBU2), J1.B12 (GND), J1.S1 (SHIELD), J2.1, J2.6, J2.11, J2.12, J2.13, J2.14, J2.15, J2.16, J2.17, J2.18, J2.19, J2.20, J2.21, J2.22, J2.23, J2.24, J2.25, J2.26, J2.27, J2.28, J2.29, J2.30, J2.31, J2.32, J2.43, J2.48, J2.49, J2.50, J2.MP, J3.2, J4.1, R6.1, R7.1, R8.1, R9.1, R24.1, R31.2, R32.2, R33.2, R34.2, R35.2, R38.1, S26.1, U1.2 (VSS), U2.2 (GND), U3.1 (GND), U4.2 (GND), U5.5 (GND), U5.10 (RES), U5.12 (GND), U6.1 (GND), U6.4 (GND), U7.49 (GND), U8.2 (GND)
IO0: Q2.3 (C2), R37.1, U7.23 (IO0)
IR_LED: R27.2, U7.13 (IO33)
IR_RX: R40.1, U7.21 (IO15)
IR_VCC: C12.1, U6.3 (Vs), U7.14 (IO25)
LCD_BL: R29.2, U7.24 (IO4)
LCD_CS: J2.38, U7.34 (IO5)
LCD_DC: J2.36, U7.28 (SD2/IO9)
LCD_EN: R28.2, U7.29 (SD3/IO10)
LCD_MOSI: J2.34, U7.36 (IO23)
LCD_SCK: J2.37, U7.35 (IO18)
unnamed: AE1.1 (A), C19.2, R36.1
unnamed: D1.1 (K), Q1.2 (S), R10.2, R23.2
unnamed: D2.2 (A), R21.2
unnamed: D3.2 (A), U7.22 (IO2)
unnamed: D3.1 (K), R38.2
unnamed: D4.1 (K), R39.2
unnamed: D5.2 (A), R1.1
unnamed: J1.A5 (CC1), R9.2
unnamed: J1.B5 (CC2), R7.2
unnamed: Q2.2 (B1), R13.2
unnamed: Q2.5 (B2), R14.2
unnamed: C16.2, Q3.3 (D), R15.2, R16.2, R17.2, R18.2
unnamed: Q3.1 (G), R25.1, R29.1
unnamed: Q4.1 (G), R26.1, R28.1
unnamed: Q5.3 (D), R1.2, R21.1
unnamed: Q5.1 (G), R20.1, R27.1
unnamed: R8.2, U1.5 (PROG)
unnamed: C3.2, R10.1, U2.1 (VIN), U2.3 (CE)
unnamed: C4.1, C24.1, U3.4 (V3), U3.16 (VCC), U8.5 (VOUT)
unnamed: R40.2, U6.2 (OUT)
unnamed: C18.2, R36.2, U7.2 (LNA_IN)
RTS: Q2.1 (E1), R14.1, U3.14 (~RTS)
SCL: J2.44, R11.1, U5.4 (SCL/SPC), U7.39 (IO22)
SDA: J2.45, R12.1, U5.6 (SDA/SDI/SDO), U7.38 (IO19)
SW_1: S1.1, S6.1, S11.1, S16.1, U7.12 (IO32)
SW_2: S2.1, S7.1, S12.1, S17.1, S22.1, U7.15 (IO26)
SW_3: S3.1, S8.1, S13.1, S18.1, S23.1, U7.16 (IO27)
SW_4: S4.1, S9.1, S14.1, S19.1, S24.1, U7.17 (IO14)
SW_5: S5.1, S10.1, S15.1, S20.1, S25.1, U7.18 (IO12)
SW_A: R31.1, S1.2, S2.2, S3.2, S4.2, S5.2, U7.6 (SENSOR_CAPP)
SW_B: R32.1, S6.2, S7.2, S8.2, S9.2, S10.2, U7.7 (SENSOR_CAPN)
SW_C: R33.1, S11.2, S12.2, S13.2, S14.2, S15.2, U7.8 (SENSOR_VN)
SW_D: R34.1, S16.2, S17.2, S18.2, S19.2, S20.2, U7.10 (IO34)
SW_E: R35.1, S22.2, S23.2, S24.2, S25.2, U7.11 (IO35)
USB_RXD: U3.2 (TXD), U7.40 (U0RXD/IO3)
USB_TXD: U3.3 (RXD), U7.41 (U0TXD/IO1)
VBUS: C1.2, C2.1, D1.2 (A), D4.2 (A), F1.2, Q1.1 (G), R6.2, U1.4 (VDD), U8.1 (VIN), U8.3 (EN)

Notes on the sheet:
DB6
ACC I2C address: 0x19
DB11
DB14
IM2
DB10
Display Interface
STAT Shutdown - High Z No Battery Present - High Z Constant Voltage - Low Charge Complete - High
LEDA
DB0
GND
DB16
TP_RES
TP_IRQ
LEDK
IM1
IOVCC
- Pull-Down resistors needed for ext1 interrupt
~{RESET}
ESP32
RTC GPIO: 0,2,4,12-15,25-27,32-39 ext0: - single RTC_GPIO as wakeup source ext1: - multiple RTC_GPIOs as wakeup source - either any pin high or all pins low - internal Pull-ups /Pull-downs disabled
IM3
DB5
Possible Replacement: LR4054-T
Extra Parts
USB-Serial Bridge
Charge current: I_CHG = 1000 / R_PROG 1000 / 3kOhm = 333mA
DB17
TP_SDA
DB7
DB12
DB1
DOTCLK
~{WR_RS}
Infrared TX / RX
SDI
DB13
DB4
Boot Mode Configuration: Pin Default Boot Download GPIO0 1 1 0 U0TXD 1 1 x GPIO2 0 x 0 GPIO4 0 x x MTDO 1 x x GPIO5 1 1 x If U0TXD, GPIO2, GPIO5 are floating, GPIO0 determines boot mode
Touch I2C address: 0x38

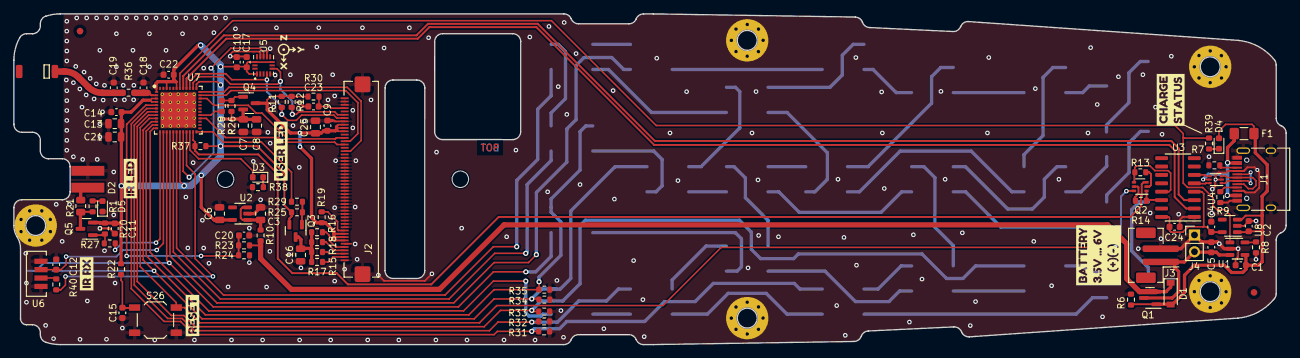
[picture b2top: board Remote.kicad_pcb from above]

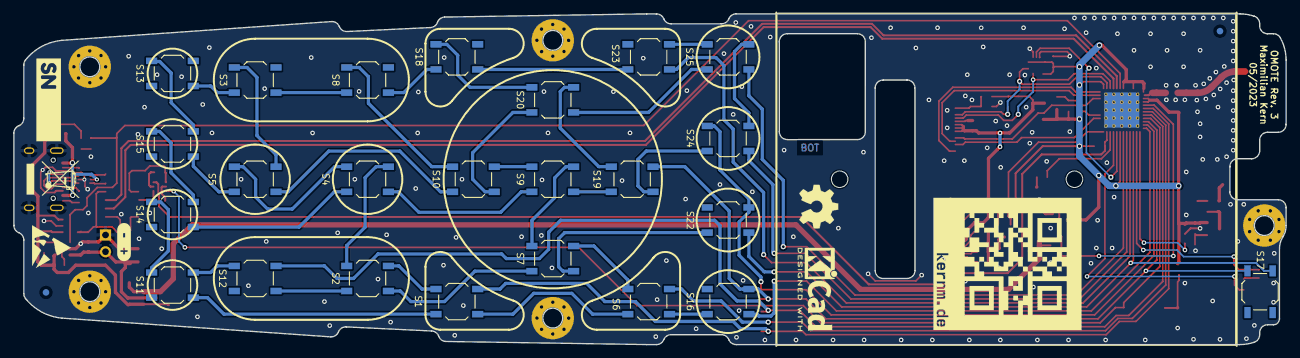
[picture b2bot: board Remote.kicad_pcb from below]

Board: 2 copper layers, 192.4 x 50.0 mm, 133 parts (29 on the bottom side), 67 nets.

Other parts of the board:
kibuzzard-63D97EAF: G***; kibuzzard-63D97EAF
kibuzzard-64A91BF0: G***; kibuzzard-64A91BF0
kibuzzard-64A91C1C: G***; kibuzzard-64A91C1C
kibuzzard-64A91C24: G***; kibuzzard-64A91C24
kibuzzard-643EE5A3: G***; kibuzzard-643EE5A3
kibuzzard-643EE5B9: G***; kibuzzard-643EE5B9
kibuzzard-643EE8B3: G***; kibuzzard-643EE8B3
kibuzzard-643EE23D: G***; kibuzzard-643EE23D
kibuzzard-643EE46C: G***; kibuzzard-643EE46C
kibuzzard-643EE532: G***; kibuzzard-643EE532
kibuzzard-643EE600: G***; kibuzzard-643EE600
kibuzzard-644014FA: G***; kibuzzard-644014FA

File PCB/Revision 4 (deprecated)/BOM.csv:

Item,Quantity,Designator,Value,Footprint,LCSC Part #,Comment
1,1,AE1,Antenna,RFANT5220110A2T,C454142,
2,11,C1; C10; C12; C14; C17; C20; C22; C23; C24; C26; C9,100nF,0603,C1591,
3,1,C11,2.2uF,0603,C913904,
4,10,C13; C16; C21; C25; C28; C3; C5; C6; C7; C8,10uF,0805,C15850,
5,3,C15; C2; C4,1uF,0603,C15849,
6,1,D1,MBR0520,D_SOD-123,C475717,
7,1,D2,SFH4547 ,LED_5mm_Side_Mount,C405273,
8,3,D3; D4; D5,LED,0603,C965807,
9,1,F1,500mA,1206,C220146,
10,1,J1,USB_C_Receptacle_USB2.0,USB_C_Receptacle_HRO_TYPE-C-31-M-12,C2982555,
12,1,J2,Conn_01x50,TFT_2.83IN_240X320_50PIN,C11098,
13,1,J3,JST_PH_B2B-PH,JST_PH_B2B-PH-SM4-TB_1x02-1MP_P2.00mm_Vertical,C160352,
14,4,Q1; Q3; Q4; Q5,DMG2301L,SOT-23,C102619,
15,1,Q2,MBT3904DW1,SOT-363_SC-70-6,C110150,
16,1,Q6,FS8205A,SOT-23-6,C908265,
17,4,R1; R39; R40; R5,2k2,0603,C114662,
18,4,R11; R12; R25; R8,4k7,0603,C99782,
19,15,R13; R14; R19; R20; R22; R23; R26; R30; R31; R32; R33; R34; R35; R37; R6,10k,0603,C98220,
20,4,R15; R16; R17; R18,10,0603,C109318,
21,1,R21,3R3,0805,C2849062,
22,3,R27; R28; R29,330,0603,C105881,
23,1,R3,1k,0603,C22548,
24,1,R36,0,0603,C116699,
25,1,R4,100,0603,C125923,
26,2,R7; R9,5.1k,0603,C105580,
27,25,S1; S10; S11; S12; S13; S14; S15; S16; S17; S18; S19; S2; S20; S22; S23; S24; S25; S26; S3; S4; S5; S6; S7; S8; S9,TL3342F160QG,SW_SPST_TL3342,C778172 ,
28,1,U1,DW01A,SOT-23-6,C18164398,
29,1,U11,TP4056,Infineon_PG-DSO-8-27_3.9x4.9mm_EP2.65x3mm,C725790,
30,1,U2,XC6220B331,SOT-23-5,C86534,
31,1,U3,CH340C,SOIC-16_3.9x9.9mm_P1.27mm,C84681,
33,1,U4,USBLC6-2P6,SOT-666,C2827693,
34,1,U5,LIS3DHTR,XDCR_LIS3DHTR,C15134,
35,1,U6,TSSP77038,Heimdall vertical,C499566,
36,1,U7,ESP32-PICO-D4,QFN-48-1EP_7x7mm_P0.5mm_EP5.3x5.3mm_ThermalVias_MR,C193707,
37,1,U8,AP2112K-3.3,SOT-23-5,C51118,
38,1,U9,MAX17048G,TDFN-8-1EP_2x2mm_P0.5mm_EP0.8x1.2mm,C2682616,
,,,,,,
39,1,,2.8 TFT Display - 240x320 with Capacitive Touchscreen,,,https://www.adafruit.com/product/2770
40,1,,3.7V 2000mAh LiPo,,,https://eckstein-shop.de/LiPo-Akku-Lithium-Ion-Polymer-Batte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
